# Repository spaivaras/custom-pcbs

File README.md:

PCB's
===========

* [SO16E-SO8N-breakout](SO16E-SO8N-breakout/) - A SO8N and SO16E breakout boards for breadboards

Software
-----------
If not stated otherwise projects are made with [**KiCad 4022 (2013-07-07)**](http://www.kicad-pcb.org)

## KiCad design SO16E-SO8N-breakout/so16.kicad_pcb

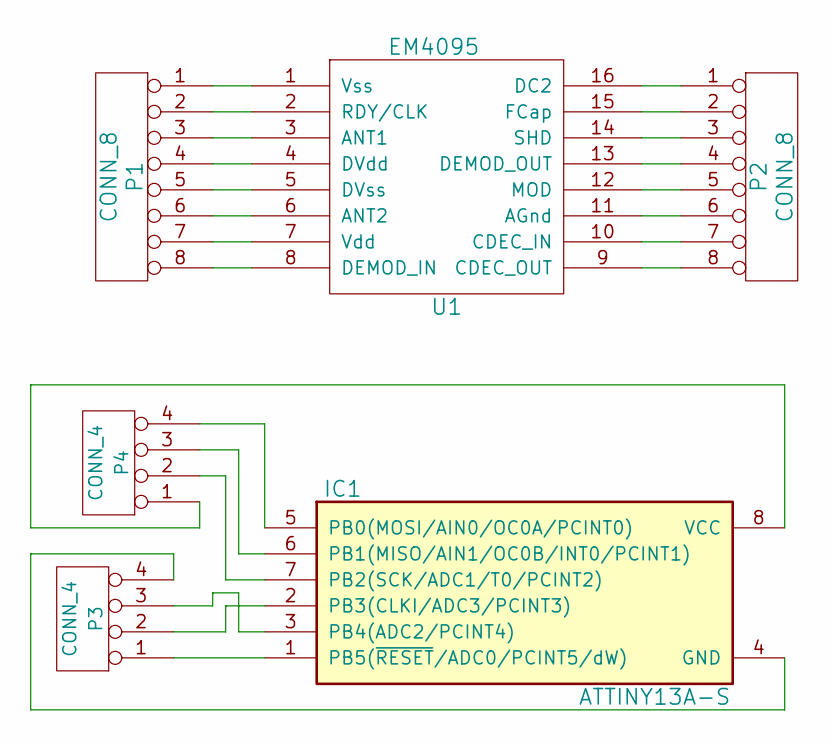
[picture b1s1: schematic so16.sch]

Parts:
IC1: ATTINY13A-S; SO8-200
P1, P2: CONN_8
P3, P4: CONN_4
U1: EM4095

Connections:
unnamed: IC1.1 (PB5(~RESET~/ADC0/PCINT5/dW)), P3.1
unnamed: IC1.2 (PB3(CLKI/ADC3/PCINT3)), P3.2
unnamed: IC1.3 (PB4(ADC2/PCINT4)), P3.3
unnamed: IC1.8 (VCC), P4.1
unnamed: IC1.4 (GND), P3.4
unnamed: P1.8, U1.8 (DEMOD_IN)
unnamed: P1.7, U1.7 (Vdd)
unnamed: IC1.5 (PB0(MOSI/AIN0/OC0A/PCINT0)), P4.4
unnamed: IC1.7 (PB2(SCK/ADC1/T0/PCINT2)), P4.2
unnamed: IC1.6 (PB1(MISO/AIN1/OC0B/INT0/PCINT1)), P4.3
unnamed: P1.6, U1.6 (ANT2)
unnamed: P2.5, U1.12 (MOD)
unnamed: P1.1, U1.1 (Vss)
unnamed: P2.1, U1.16 (DC2)
unnamed: P2.2, U1.15 (FCap)
unnamed: P2.3, U1.14 (SHD)
unnamed: P2.4, U1.13 (DEMOD_OUT)
unnamed: P2.6, U1.11 (AGnd)
unnamed: P2.7, U1.10 (CDEC_IN)
unnamed: P2.8, U1.9 (CDEC_OUT)
unnamed: P1.5, U1.5 (DVss)
unnamed: P1.4, U1.4 (DVdd)
unnamed: P1.3, U1.3 (ANT1)
unnamed: P1.2, U1.2 (RDY/CLK)

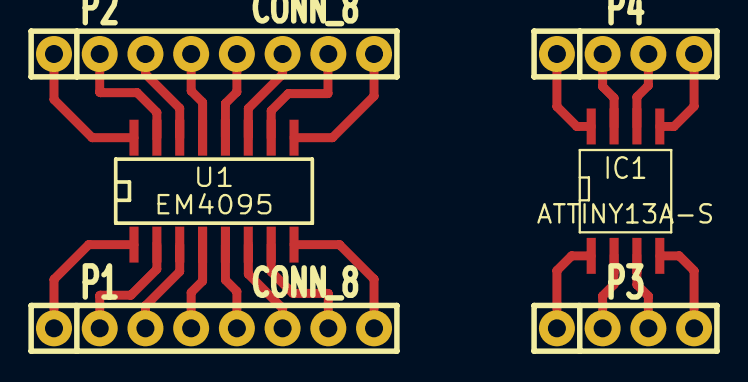
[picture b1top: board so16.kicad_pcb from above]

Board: 2 copper layers, 6 parts (0 on the bottom side), 24 nets.

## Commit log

2014-08-14 SO8N and SO16E breakout boards for breadboards
